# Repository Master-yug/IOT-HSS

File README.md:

Still working on it...just some minor tweakings and updates

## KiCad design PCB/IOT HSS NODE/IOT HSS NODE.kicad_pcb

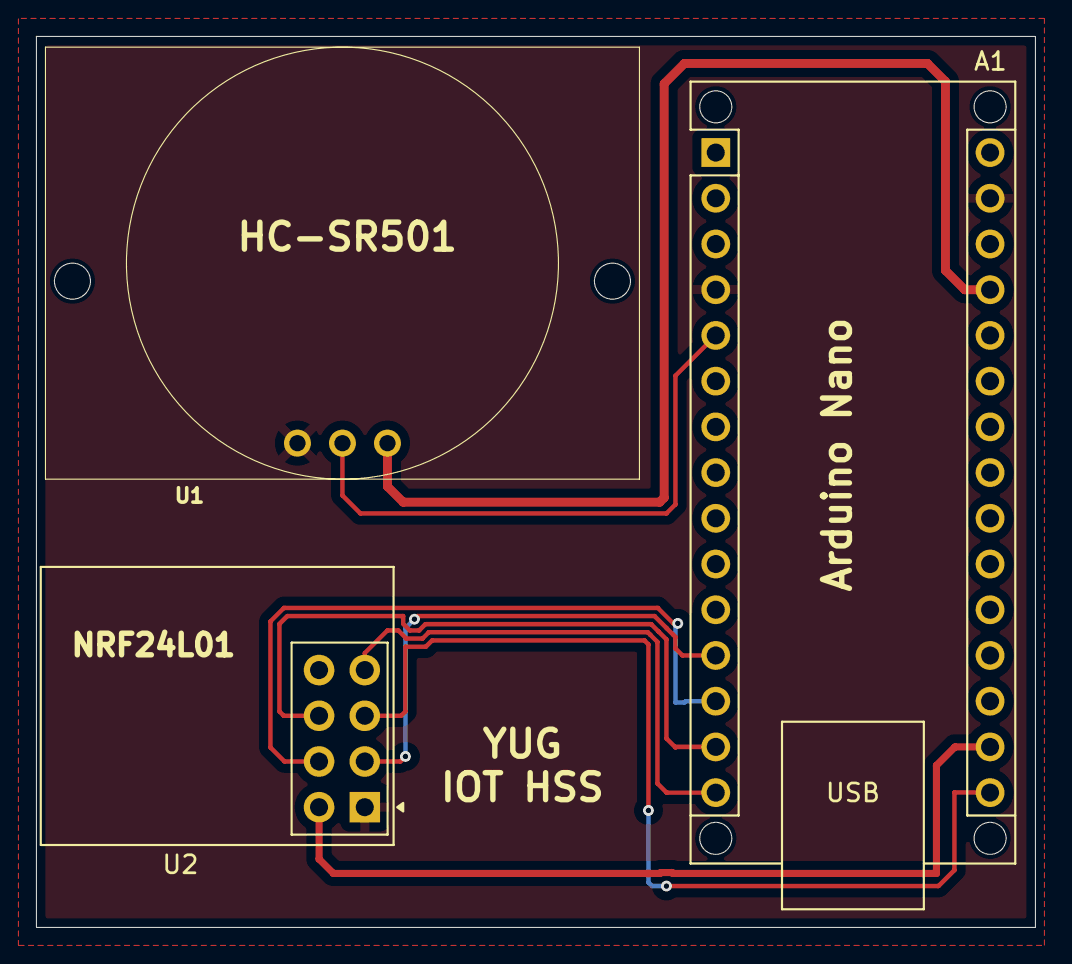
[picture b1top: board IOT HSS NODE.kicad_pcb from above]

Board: 2 copper layers, 55.5 x 49.5 mm, 3 parts (0 on the bottom side), 9 nets.

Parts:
A1: Arduino_Nano_v3.x; Arduino_Nano_WithMountingHoles
U1: HC-SR501
U2: NRF24L01; nRF24L01_Breakout(BORDER)

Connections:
+3.3V: A1.17 (3V3), U2.2 (VCC)
+5V: A1.27 (+5V), U1.3 (VCC)
GND: A1.4 (GND), A1.29 (GND), U1.1 (GND), U2.1 (GND)
unnamed: A1.5 (D2), U1.2 (OUT)
unnamed: A1.12 (D9), U2.3 (CE)
unnamed: A1.13 (D10), U2.4 (~CSN)
unnamed: A1.14 (D11), U2.6 (MOSI)
unnamed: A1.15 (D12), U2.7 (MISO)
unnamed: A1.16 (D13), U2.5 (SCK)

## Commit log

2025-08-09 Added server.py
2025-08-09 Added hub and node
2025-08-10 Updated Files
    - No “no motion” messages anymore.
    - Node ID in transmitter is now one variable — we can change it once to make a new node.
    - Receiver zone mapping is in a struct array, so we can just add a new line for a new node.
    - Logic verified:
    Motion → sends N#:1 → receiver posts JSON to Flask.
    No motion → nothing sent.
2025-08-11 Added HSS Dashboard
    Added index.html and login.html
2025-08-11 Update index.html
    Fixing timestamp error
2025-08-16 Update login.html
    Minor changes to login.html
2025-08-22 Switch from Firestore to Realtime Database
    Updated Firebase integration to use Realtime Database instead of Firestore and modified UI elements accordingly.
2025-08-22 Refactor login.html for improved styling and error handling
2025-08-24 Added PCB files
2025-08-24 Added PCB directory
2025-08-25 Add initial content to README.md
2025-08-25 Added KiCad project files
2025-08-25 Added symbols and footprints
2025-08-26 Update README with minor tweaks and updates
2025-08-30 Added ESP32 DEVKIT
2025-08-30 Added HUB ESP32 KiCad files
